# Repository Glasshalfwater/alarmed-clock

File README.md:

# Integral Clock
### A WiFi-capable alarm clock that can play "music" and annoy you with math until you wake up.
This project's aim is to create an alarm clock capable of playing basic music, linking to other sensors over wifi, and throwing math problems at the target subject until they have no choice but to wake up. 

The current implementation features a 2.8" TFT display with 3 buttons for input (selecting answers, setting alarm, etc.) and a 420 mAh LiPo battery for travel purposes enclosed in a durable PETG casing. The only way to turn off the alarm planned right now is to be solving definite integrals. Future plans include connectivity to other modules over WiFi to require the person being subjected to this to leave the room (or maybe the house, on a morning run or similar activities) or perform other activities to ensure that they are in fact, awake, and will not return to bed.

NOTE FOR REVIEWERS: I am using a mix of parts with some that are not in the kit of parts from BLARE that I already own or intend to purchase myself. Sourcing for all parts is denoted in the BOM below and in the .csv file.

### Origin:

To be honest, I struggle with getting out of bed when my alarm goes off. I typically hit snooze at least once (or thrice) before getting out of bed as late as possible. Moving my alarm to other rooms really isn't an option and I have demonstrated that I am capable of crossing the room, digging through drawers, turning off my alarm, and going back to bed. Thus, in perhaps an overengineered fashion I decided to make my own alarm clock without a snooze function (or an off button).

I have yet to test the most effective method of inducing body temperature rise (and thus waking up) but science seems to suggest that exercise and cold showers immediately after waking up are some of the best options. Given that I have no desire to make the only method of turning off my alarm to take a cold shower in the morning, and I currently don't have a method of verifying exercising over WiFi (I may link the ESP32S3 to a watch over bluetooth or add a beam break at the door), my current plan is to use force mental exertation in order to wake my brain up (i.e. math problems). (Although, I may train a model like YOLO-8 to recognize jump roping and simply use an outdoor camera to verify physical activity, again, could be dangerous during the winter months though) 

Of course, the difficulty of the math problems have to be carefully chosen such as to be challenging enough that I can't perform them and then return to sleep (i.e. basic multiplication, simple algebra, basic derivatives, etc.) but also reasonable to complete in, say, 3 minutes after just waking up. Of course, proofs are also unable to be used because of a lack of processing power and sufficient input methods on the alarm clock. Currently I'm planning on using definite integrals to force myself to go through multiple steps per problem (while also not being too difficult, likely won't do anything past inverse trig equations) and also to force myself to use paper and pencil. This of course has the added benefit of keeping me in practice with regards to single-variable calculus.

## Wiring Schematic

## PCB
### Top Layer:

### Bottom Layer:

### 3D View Top:

### 3D View Bottom:

## CAD
### Design completed in Onshape

[Document Link](https://cvilleschools.onshape.com/documents/9dc3dff3a2d00cce4e52e484/w/d224b5bf15cdee65343ba0da/e/0274f1c24004c26469ea7ce8?renderMode=0&uiState=6aefdacb49cd08c4fdbf94c6)

Isometric:

Front:

Back:

Top:

Bottom (port):

Sides:

## PCB Order 
Via JLCPCB:

### BOM
|Quantity|Description                      |Price                                               |Purpose                                                                               |Manufacturer        |Supplier                              |Link                                                                                                                                                                                                                                                                                                                                                                                                                                                                                                                                                                                                                     |FIELD8|
|--------|---------------------------------|----------------------------------------------------|--------------------------------------------------------------------------------------|--------------------|--------------------------------------|-------------------------------------------------------------------------------------------------------------------------------------------------------------------------------------------------------------------------------------------------------------------------------------------------------------------------------------------------------------------------------------------------------------------------------------------------------------------------------------------------------------------------------------------------------------------------------------------------------------------------|------|
|1       | XIAO ESP32S3 Plus               | $7.90                                              | MCU to communicate to WiFi and run code                                              | Seeed Studio       | Seeed Studio                         | https://www.seeedstudio.com/Seeed-Studio-XIAO-ESP32S3-Plus-p-6361.html?srsltid=AYCX9vJxZSAwjrUI7pF0ljs7JlnbIa4n6NOk-60a7d-rv-yQvqUlJJ96                                                                                                                                                                                                                                                                                                                                                                                                                                                                                 |      |
|3       | Kailh Choc 2 Keyswitches        | $0.6 per (3 needed)                                | Button input                                                                         | Kailh              | Amazon (Currently Owned)             | https://www.amazon.com/KAILH-Profile-Mechanical-Keyboard-Keystem/dp/B0B463YXGQ/ref=sr_1_1_sspa?dib=eyJ2IjoiMSJ9.wxFdw1Pe7LOSd966UxVZUcDKomHLuleLIcXTQ4C0H2OYvQuT6RBjL9nNYi-8R9i4hKspNWTHWkpp5UTh7RcvgwtB2-XZpqW57wmhBzVCubamU9ifGvLU4fsc5gY4zMSOE4ZC4DMauPttKu-EcYQpunBiSKjQ7Bb7eE-JyNmWT34IKr3XreAA5Uih6Pkxwsu5_BBwKSwNySoJsfGGG-lP7ZRqvkA1rQauyjz1yVmmQBw.MvRmVcVKc9_-DKk9rJdhjHAi8Og3_gsiFY7_3GpMbQ0&dib_tag=se&keywords=kailh+choc+v2&qid=1794098954&sr=8-1-spons&sp_csd=d2lkZ2V0TmFtZT1zcF9hdGY&psc=1                                                                                                                          |      |
|3       | Cherry MX Style Blank Keycaps   | $10 per 10 units (3 needed)                        | Button clicky comfort                                                                | PATIKIL            | Amazon (Currently Owned)             | https://www.amazon.com/PATIKIL-Universal-Replacement-Accessories-Mechanical/dp/B0B5KZQ9X9/ref=sr_1_7_sspa?crid=12ATOS6KH7DQS&dib=eyJ2IjoiMSJ9.-PEZO3lmrldqZH0to2R2HRwN5BKRn86UWDtIm__w3eBpasSO6ZcCaM8QUq_QC9RgCpf5S-4EZqDYFlEzHrvcDUFbGRBe5v_g-2uizBUqArkQR8r0fBgW3fjjAHnhHtVhcrmu-O6b1ETLkijcrdWsNscyHGEe1Wfe2qANjGtk2DE58KXFpQiHFqz2rpJbc1Yo6SbPw8HZisYYzNHv0vWksAsGGalZiP4I_vSb9mQW3ls.IQFXB0KRTVGAZzOyLXqZZXrNk55Y8BOvogiIjWzgNds&dib_tag=se&keywords=Cherry%2BMX%2BKeycaps%2Bblank%2B10pcs&qid=1788231734&sprefix=cherry%2Bmx%2Bkeycaps%2Bblank%2B10pcs%2Caps%2C93&sr=8-7-spons&sp_csd=d2lkZ2V0TmFtZT1zcF9tdGY&th=1|      |
|1       | Shillehtek 2.8" TFT Display     | $10.99                                             | Displaying information; SD card data storage                                         | Shillehtek         | Shillehtek                           | https://shillehtek.com/products/2-8-spi-tft-lcd-touch-screen-module-240x320-ili9341-for-arduino?srsltid=AYCX9vIh7LBUbMqbMsmKVdWfoJGANU9fe-zuG7ylrXbS2I1idACA-6uZ                                                                                                                                                                                                                                                                                                                                                                                                                                                        |      |
|1       |  1x4 Male Header Pin            | $0.36                                              | Holding up other side of screen (the display comes with one) (and SD card connection)| Digikey            | Hack Club (BLARE kit)                | https://www.digikey.com/en/products/detail/amphenol-icc-fci-/77311-118-04LF/1523799?gclsrc=aw.ds&gad_source=1&gad_campaignid=20504594076&gbraid=0AAAAADrbLlhrE__MGVZ1djlg2N_s4QS_C&gclid=CjwKCAiAtbvXBhB_EiwAjwv9Jqfx1JAz7Fl8_0-0TrCNKfjLfloNJBBTnrZEMnRciTCU1dFRIJ7HDRoCcR0QAvD_BwE                                                                                                                                                                                                                                                                                                                                    |      |
|1       | Passive Piezoelectric Buzzer    |  $1.5                                              | Playing alarm and "music"                                                            | Adafruit Industries| Hack Club (BLARE kit)                | https://www.adafruit.com/product/160?srsltid=AYCX9vJh_QuNLozkjfWoHRwfDYuFgT-AlzdaMG031J6YqCmVwYJ4LiPj                                                                                                                                                                                                                                                                                                                                                                                                                                                                                                                   |      |
|1       |  JST 2-pin header               | $0.72 for 20                                       | Connecting battery cable                                                             | JST                | LCSC.com                             | https://www.lcsc.com/product-detail/C131337.html?s_z=n_q_C131337&globalKeyword=C131337                                                                                                                                                                                                                                                                                                                                                                                                                                                                                                                                  |      |
|1       | 3.7v LiPo Battery w/ Short Cable| $6.95                                              | Powering circuit when not connected over USB-C                                       | Adafruit Industries| Adafruit Industries                  | https://www.adafruit.com/product/4236                                                                                                                                                                                                                                                                                                                                                                                                                                                                                                                                                                                   |      |
|1       | PETG Filament for Case          | ~$1.5 (~$0.03 per gram for ~43 grams at 50% infill)| Protecting circuit and PCB                                                           | Bambu              | Bambu A1 Mini or P1S (free access to)| https://us.store.bambulab.com/products/petg-basic?id=738167451007287326&skr=yes&srsltid=AYCX9vKs56FvN0TbogePtkfMKkGFU-8XHuPbflE_q1Ne9i5W7lo3gTJMRZw                                                                                                                                                                                                                                                                                                                                                                                                                                                                     |      |

## Credits
This project was created as for Hack Club's BLARE YSWS (blare.hackclub.com) as a part of Hack Club and NASA's Stardance program which was a 6 month long program where teens built (and shipped!) technical projects and got cool stuff in return (stardance.hackclub.com)! Hack Club is a non-profit that runs really awesome programs for teenagers, if you're a teen reading this, you should give it a shot! https://www.hackclub.com

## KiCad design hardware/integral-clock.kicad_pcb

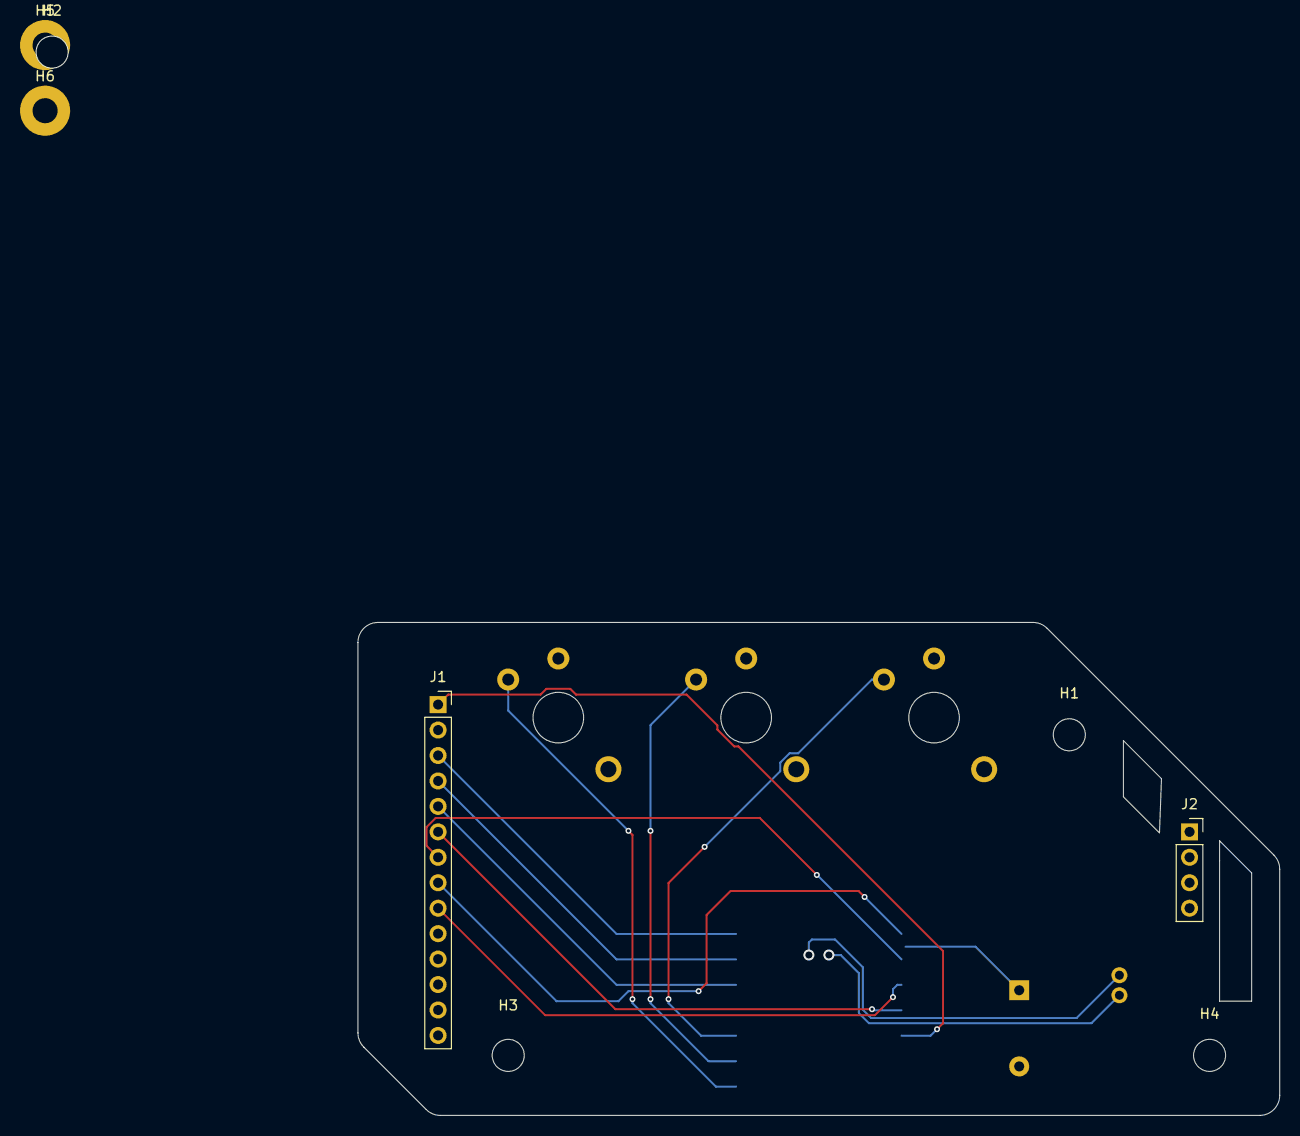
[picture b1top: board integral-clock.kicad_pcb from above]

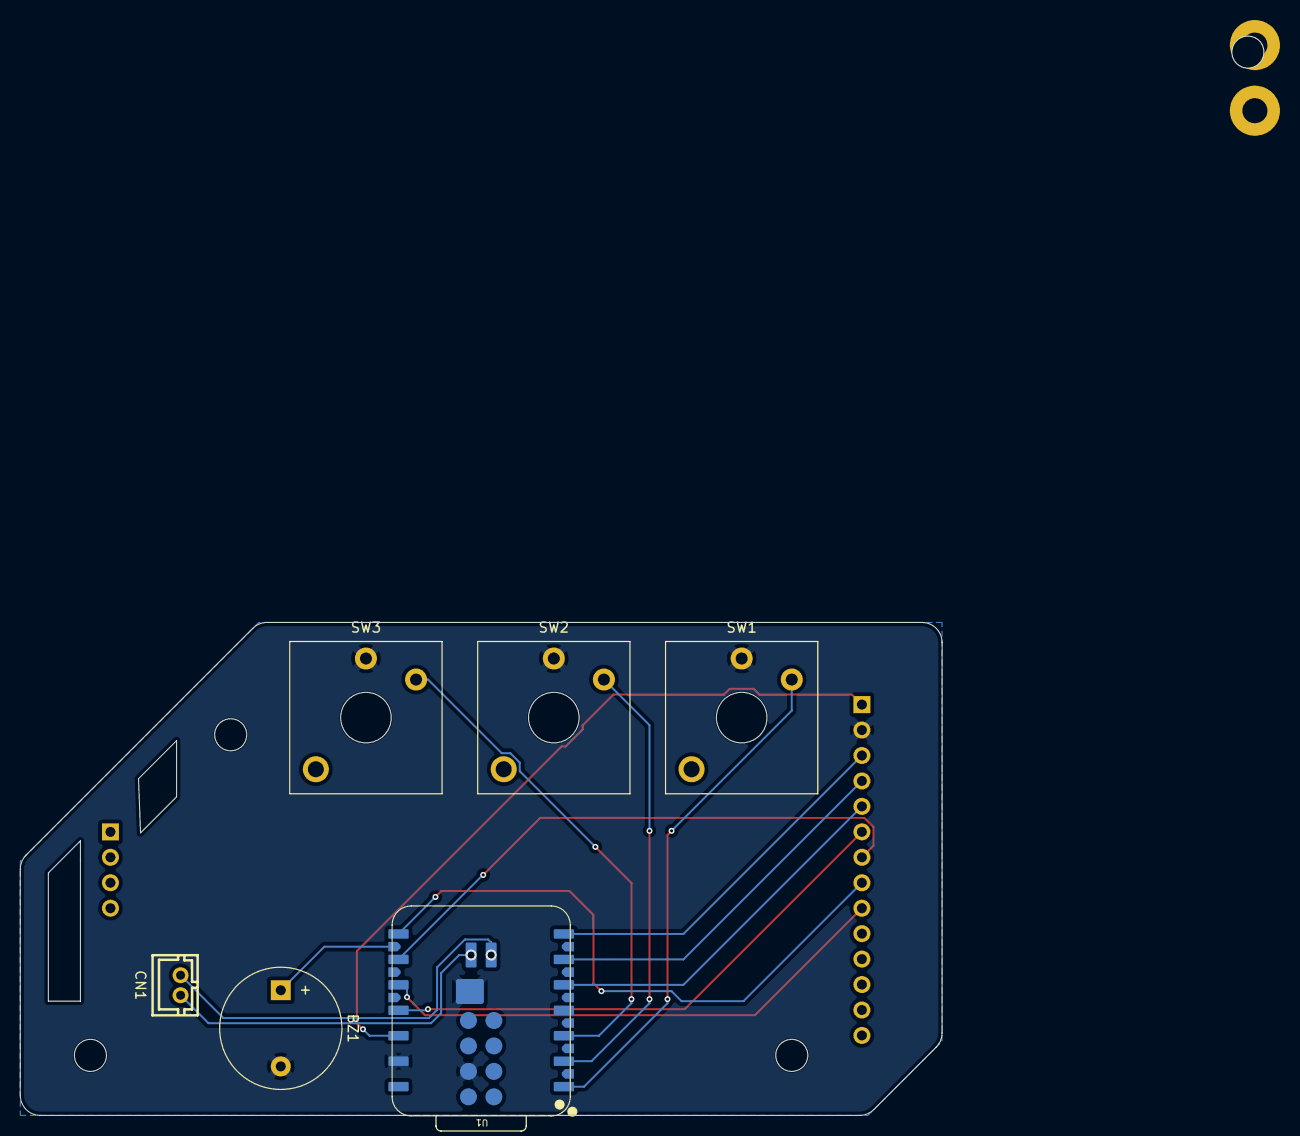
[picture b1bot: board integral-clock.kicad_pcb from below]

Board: 2 copper layers, 92.0 x 49.2 mm, 14 parts (6 on the bottom side), 15 nets.

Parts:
BZ1: Buzzer; Buzzer_12x9.5RM7.6
CN1: B2B-PH-K-S; CONN-TH_B2B-PH-K-S
H1, H2, H3, H4: MountingHole; MountingHole_3.2mm_M3
H5, H6: MountingHole_Pad; MountingHole_2.5mm_Pad
J1: Conn_01x14_Socket; PinSocket_1x14_P2.54mm_Vertical
J2: Conn_01x04_Pin; PinSocket_1x04_P2.54mm_Vertical
SW1, SW2, SW3: SW_Push; SW_Kailh_Choc_V2_1.00u
U1: XIAO-ESP32-S3-Plus-SMD

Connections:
+3V3: J1.1, U1.12 (3V3_OUT)
+BATT: CN1.1, H5.1 (1_1), U1.32 (VBAT)
-BATT: CN1.2, H6.1 (1_1), U1.33 (GND)
/CS: J1.3, U1.7 (D6)
/D/C: J1.5, U1.5 (D4)
/LED: J1.8, U1.8 (D7)
/RST: J1.4, U1.6 (D5)
/SCK: J1.7, U1.9 (D8)
/SDI/MOSI: J1.6, U1.11 (D10)
/SDO/MISO: J1.9, U1.10 (D9)
GND: BZ1.2 (-), J1.2, SW1.1, SW2.1, SW3.1, U1.13 (GND), U1.27 (GND), U1.34 (PAD)
unnamed: BZ1.1 (+), U1.21 (D19)
unnamed: SW1.2, U1.1 (D0)
unnamed: SW2.2, U1.2 (D1)
unnamed: SW3.2, U1.3 (D2)
